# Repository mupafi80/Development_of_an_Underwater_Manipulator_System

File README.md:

# Development_of_an_Underwater_Manipulator_System
This repository documents the development of an underwater manipulator. It includes the design methodology, material selection for mechanical construction, electronic system components, software development, and the physical assembly of the manipulator. Design files for the manipulator arm components and electrical connection diagrams are available in this repository. This project is part of the doctoral thesis of PhD Salatiel García Nava.

The proposed arm structure and link dimensions are presented below.

The components of a link in the robotic arm, including sections of tubing, flanges, and seals, are observed.

Assembled links: the first one includes the o-rings between the threaded sections, while the lower two display the connecting threads.

García Nava, Salatiel (2025). Desarrollo de un brazo manipulador subacuático. Centro de Investigación y de Estudios Avanzados del IPN. Directores de tesis: Dr. Filiberto Muñoz Palacios, Dr. Sergio Rogelio Lozano Leal. Tesis de doctorado

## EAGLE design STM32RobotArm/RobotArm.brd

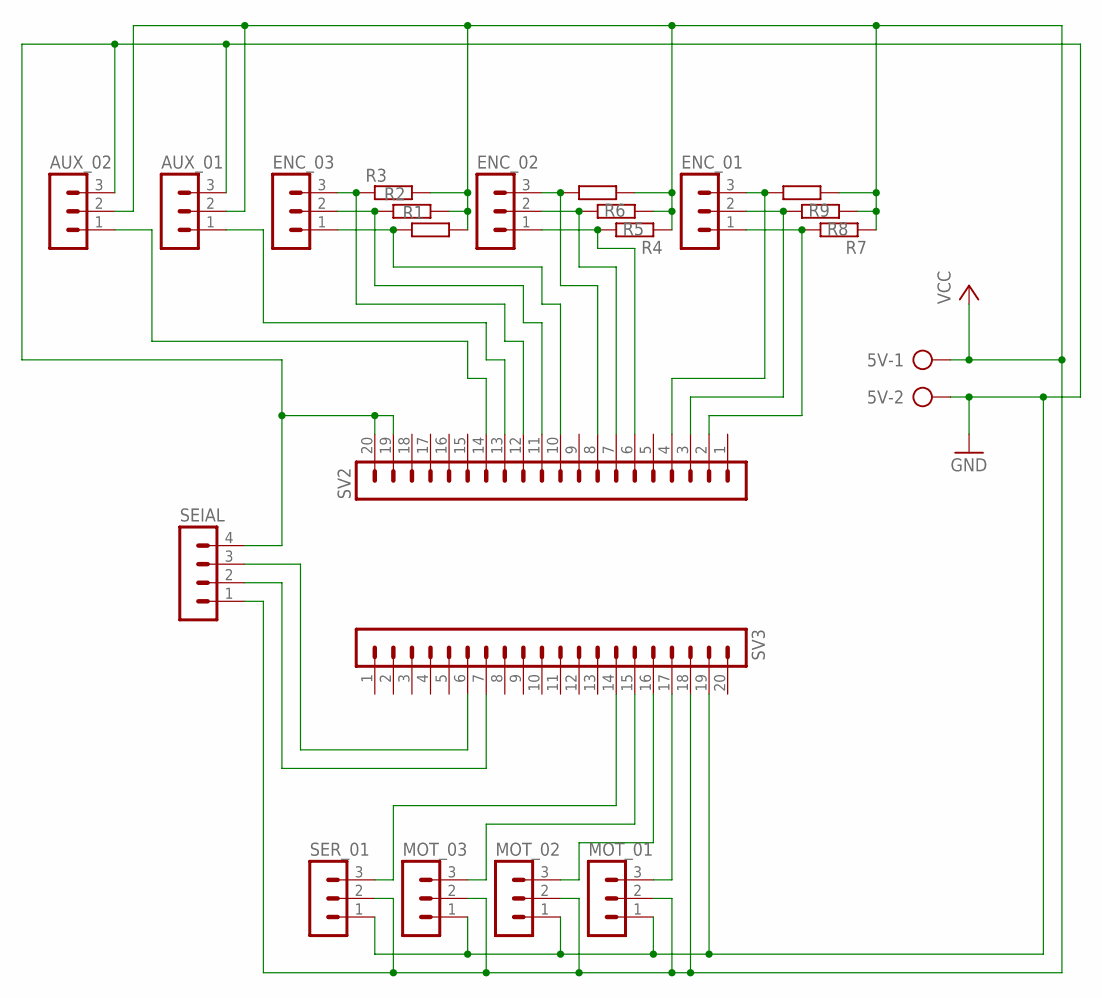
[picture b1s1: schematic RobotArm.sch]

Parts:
5V: AK500/2-H
AUX_01, AUX_02: MA03-1
ENC_01, ENC_02, ENC_03: MA03-1
MOT_01, MOT_02, MOT_03: MA03-1
R1, R2, R3, R4, R5, R6, R7, R8, R9: R-EU_0207/10; 0207/10
SEIAL: MA04-1
SER_01: MA03-1
SV2, SV3: MA20-1

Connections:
GND: 5V.2, AUX_01.3, AUX_02.3, MOT_01.1, MOT_02.1, MOT_03.1, SEIAL.4, SER_01.1, SV2.19, SV2.20, SV3.19
unnamed: ENC_01.3, R9.2, SV2.4
unnamed: ENC_01.2, R8.2, SV2.3
unnamed: ENC_01.1, R7.2, SV2.2
unnamed: ENC_02.3, R6.2, SV2.8
unnamed: ENC_02.2, R5.2, SV2.7
unnamed: ENC_02.1, R4.2, SV2.6
unnamed: ENC_03.3, R3.1, SV2.12
unnamed: ENC_03.2, R2.1, SV2.11
unnamed: ENC_03.1, R1.1, SV2.10
unnamed: AUX_01.1, SV2.13
unnamed: AUX_02.1, SV2.14
unnamed: MOT_01.3, SV3.17
unnamed: MOT_02.3, SV3.16
unnamed: MOT_03.3, SV3.15
unnamed: SER_01.3, SV3.14
unnamed: SEIAL.2, SV3.7
unnamed: SEIAL.3, SV3.6
VCC: 5V.1, AUX_01.2, AUX_02.2, MOT_01.2, MOT_02.2, MOT_03.2, R1.2, R2.2, R3.2, R4.1, R5.1, R6.1, R7.1, R8.1, R9.1, SEIAL.1, SER_01.2, SV3.18

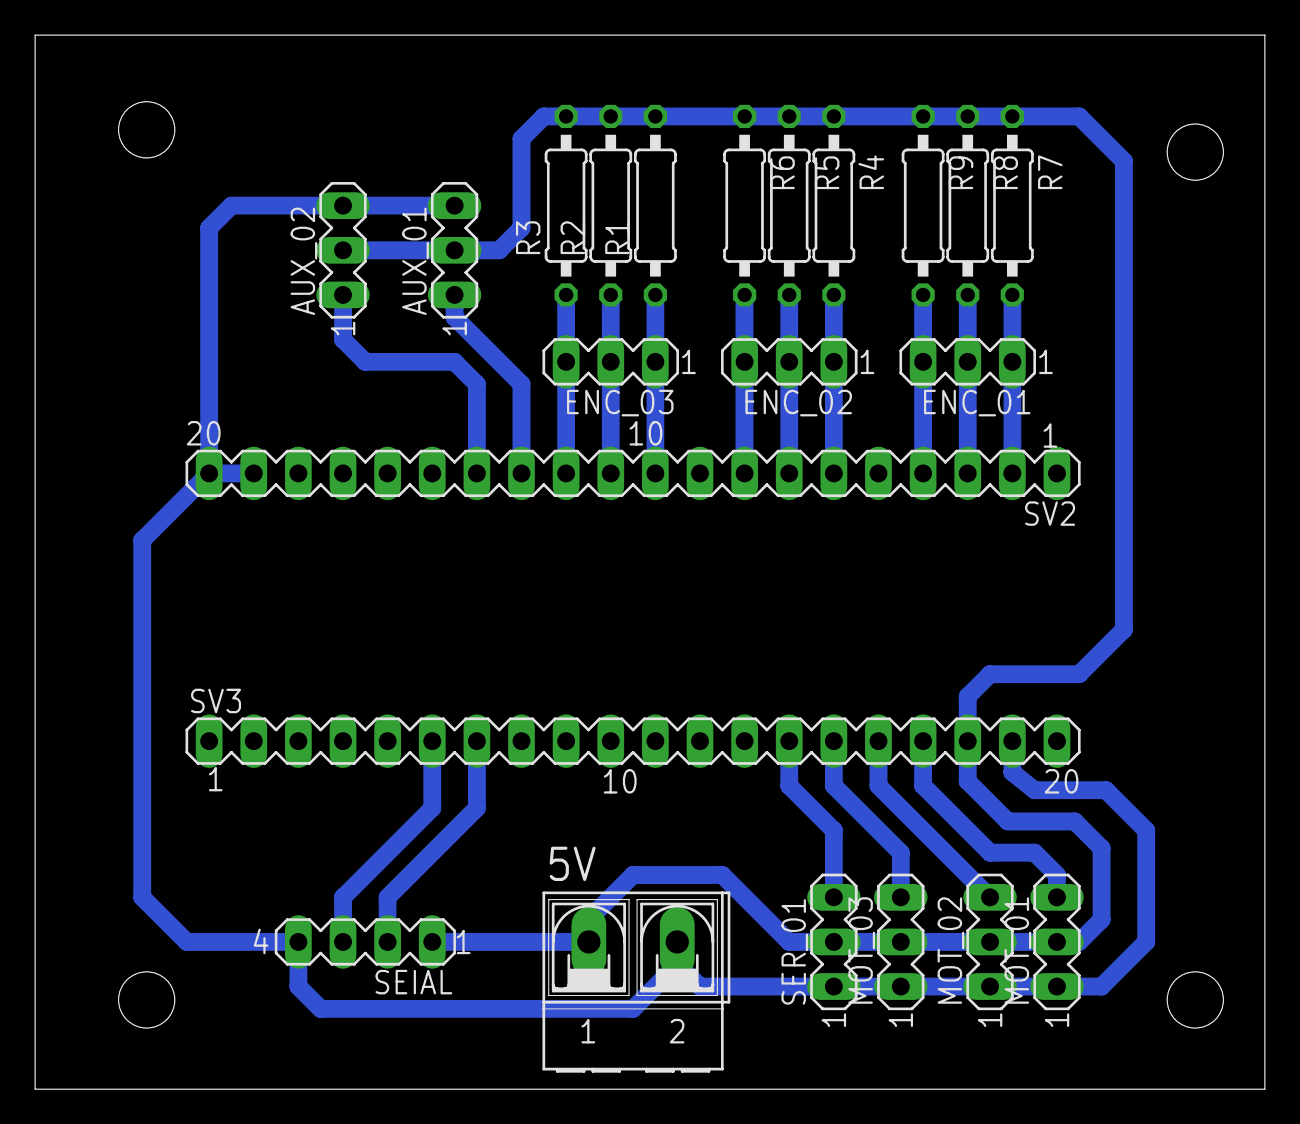
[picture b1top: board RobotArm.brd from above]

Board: 2 copper layers, 70.0 x 60.0 mm, 22 parts (0 on the bottom side), 19 nets.
